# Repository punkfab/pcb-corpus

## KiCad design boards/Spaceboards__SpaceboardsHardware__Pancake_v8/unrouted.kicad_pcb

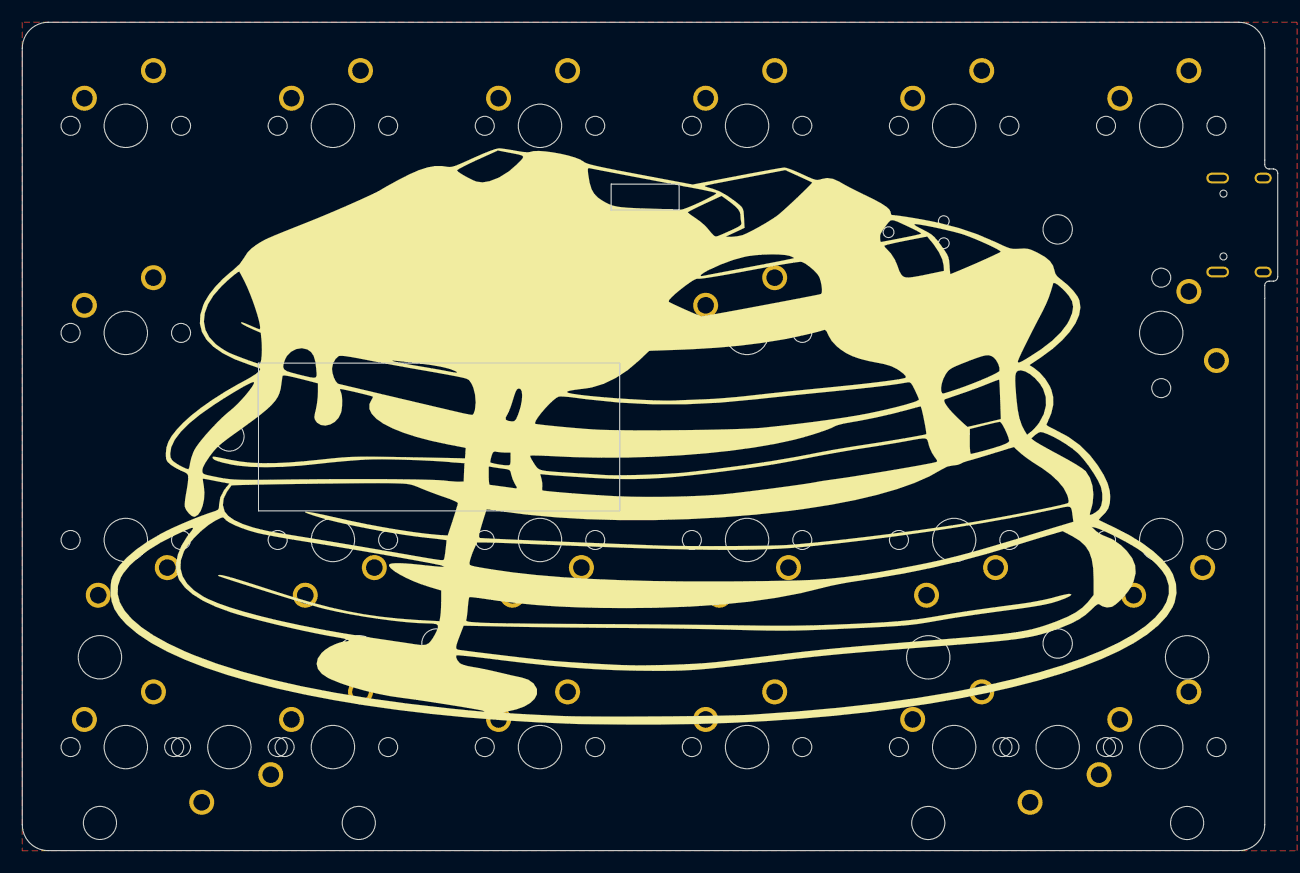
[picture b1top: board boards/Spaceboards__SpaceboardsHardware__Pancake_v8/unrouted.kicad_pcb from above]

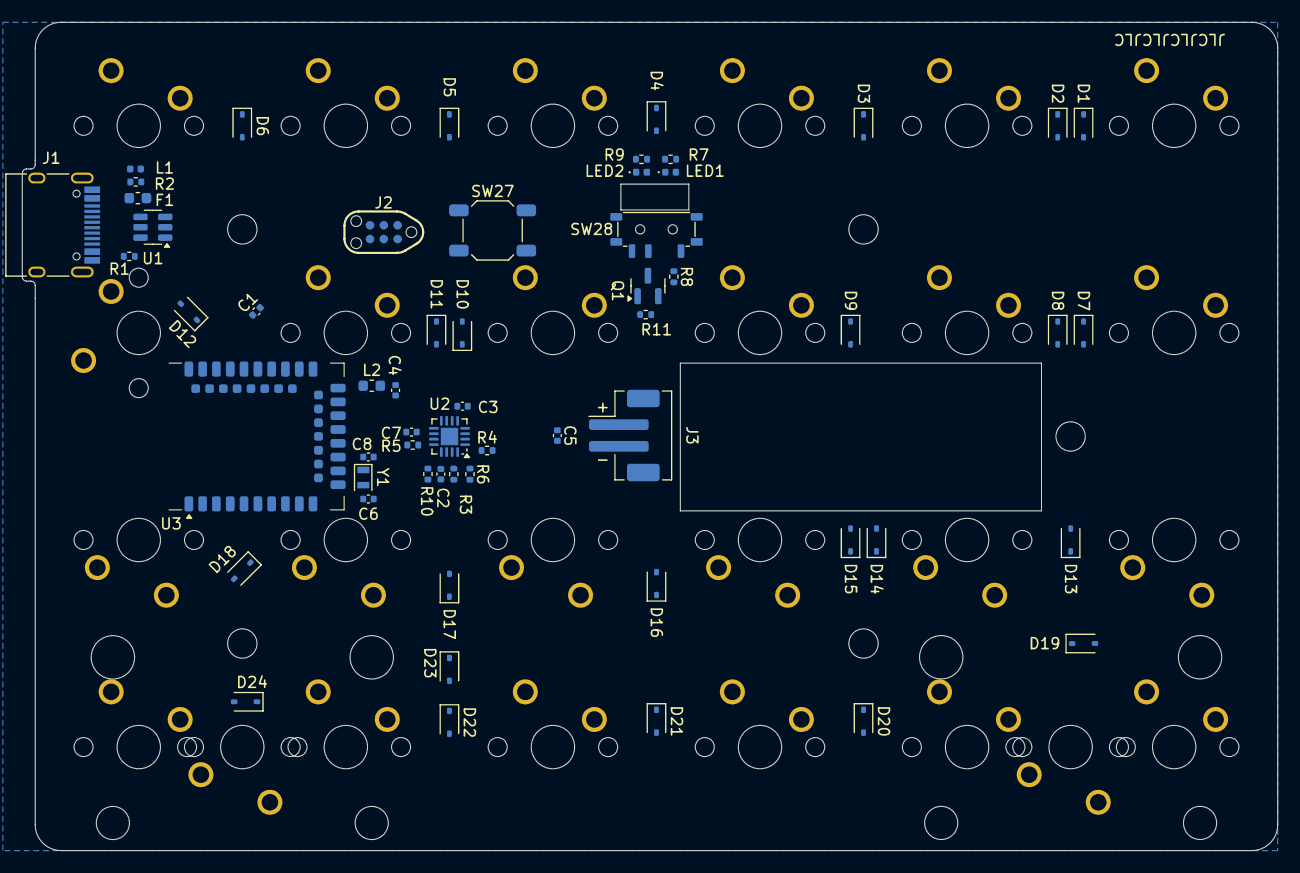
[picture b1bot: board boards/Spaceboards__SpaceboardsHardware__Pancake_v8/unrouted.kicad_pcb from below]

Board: 2 copper layers, 115.5 x 76.2 mm, 91 parts (58 on the bottom side), 62 nets, no tracks yet.

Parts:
C1, C2, C3, C5, C7: 4u7; C_0402_1005Metric
C4: 1u; C_0402_1005Metric
C6, C8: 12p; C_0402_1005Metric
D1, D2, D3, D4, D5, D6, D7, D8, D9, D10, D11, D12, D13, D14, D15, D16, D17, D18, D19, D20, D21, D22, D23, D24: D_Small; D_SOD-323
F1: 750 mA; Fuse_0603_1608Metric
H1, H2, H3, H4, H5: MountingHole; MountingHole_2.7mm_M2.5
J1: HRO_TYPE-C-31-M-14; USB_C_Receptacle_HRO_TYPE-C-31-M-12
J2: TC2030_SWD; CON_TC2030_outlined
J3: Battery; JST_PH_B2B-PH-SM4-TB_1x02-1MP_P2.00mm_Vertical
L1: BLM15PX121SN1D; L_0402_1005Metric
L2: 10 uH; L_0603_1608Metric
LED1: Orange; LED_0402_1005Metric
LED2: Blue; LED_0402_1005Metric
Q1: 2N7002; SOT-23
R1, R2: 5k1; R_0402_1005Metric
R3: 47k; R_0402_1005Metric
R4, R7, R9, R11: 10k; R_0402_1005Metric
R5: 1k5; R_0402_1005Metric
R6: 3k9; R_0402_1005Metric
R8: 100k; R_0402_1005Metric
R10: 100R; R_0402_1005Metric
S1, S2: MX_stab; STAB_MX_2u
SW1, SW2, SW3, SW4, SW5, SW6, SW7, SW8, SW9, SW10, SW11, SW12, SW13, SW14, SW15, SW16, SW17, SW18, SW19, SW20, SW21, SW22, SW23, SW24, SW25, SW26: SW_Push_45deg; SW_MX_1u
SW27: RST; SW_SPST_SKQG_WithStem
SW28: PWR; SW_MSK12C02-HB
U1: SRV05-4; SOT-23-6
U2: BQ24075; VQFN-16-1EP_3x3mm_P0.5mm_EP1.6x1.6mm
U3: nRF52840_E73-2G4M08S1C
Y1: 32.768 KHz; Crystal_SMD_2012-2Pin_2.0x1.2mm

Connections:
+5V: C1.1, C2.1, F1.1, R10.1, U1.5 (VP), U2.13 (IN), U3.27 (VBUS)
+BATT: C5.1, J3.1, R8.2, U2.2 (BAT), U2.3 (BAT)
+VSW: C3.1, C7.1, LED1.2 (A), U2.6 (EN1), U2.10 (OUT), U2.11 (OUT), U3.23 (VDDH)
/ILIM: R5.1, U2.12 (ILIM)
/TMR: R3.1, U2.14 (TMR)
BOOT: R9.1, U3.10 (P0.30/AIN6)
DCCH: L2.1, U3.25 (DCCH)
GND: C1.2, C2.2, C3.2, C4.2, C5.2, C6.2, C7.2, C8.2, J1.A1 (GND), J1.A12 (GND), J1.B1 (GND), J1.B12 (GND), J1.S1 (SHIELD), J2.5 (GND), J3.2, LED2.1 (K), Q1.2 (S), R1.1, R2.1, R3.2, R4.2, R5.2, R6.2, R11.2, SW27.2, SW28.3 (C), U1.2 (VN), U2.4 (~CE), U2.5 (EN2), U2.8 (VSS), U2.17 (VSS), U3.5 (GND), U3.21 (GND), U3.24 (GND)
unnamed: D1.2 (A), SW1.1
unnamed: D2.2 (A), SW2.1
unnamed: D3.2 (A), SW3.1
unnamed: D4.2 (A), SW4.1
unnamed: D5.2 (A), SW5.1
unnamed: D6.2 (A), SW6.1
unnamed: D7.2 (A), SW7.1
unnamed: D8.2 (A), SW8.1
unnamed: D9.2 (A), SW9.1
unnamed: D10.2 (A), SW10.1
unnamed: D11.2 (A), SW11.1
unnamed: D12.2 (A), SW12.1
unnamed: D13.2 (A), SW13.1
unnamed: D14.2 (A), SW14.1
unnamed: D15.2 (A), SW15.1
unnamed: D16.2 (A), SW16.1
unnamed: D17.2 (A), SW17.1
unnamed: D18.2 (A), SW18.1
unnamed: D19.2 (A), SW19.2, SW20.1
unnamed: D20.2 (A), SW21.1
unnamed: D21.2 (A), SW22.1
unnamed: D22.2 (A), SW23.1
unnamed: D23.2 (A), SW24.1
unnamed: D24.2 (A), SW25.2, SW26.1
unnamed: F1.2, L1.2
unnamed: J1.A5 (CC1), R2.2
unnamed: J1.B5 (CC2), R1.2
unnamed: LED1.1 (K), R7.2
unnamed: LED2.2 (A), R9.2
unnamed: Q1.1 (G), R10.2, R11.1
unnamed: R8.1, SW28.1 (A)
unnamed: R6.1, U2.16 (ISET)
unnamed: R4.1, U2.1 (TS)
unnamed: R7.1, U2.9 (~CHG)
unnamed: C6.1, U3.11 (P0.00/XL1), Y1.2
unnamed: C8.1, U3.13 (P0.01/XL2), Y1.1
RST: J2.3 (~RST), SW27.1, U3.26 (P0.18/~RESET)
SWDCLK: J2.4 (SWCLK), U3.39 (SWDCLK)
SWDIO: J2.2 (SWDIO), U3.37 (SWDIO)
SYSOFF: Q1.3 (D), SW28.2 (B), U2.15 (SYSOFF)
USB-D+: J1.A6 (D+), J1.B6 (D+), U1.6 (IO4), U3.31 (D+)
USB-D-: J1.A7 (D-), J1.B7 (D-), U1.1 (IO1), U3.29 (D-)
VBUS: J1.A4 (VBUS), J1.A9 (VBUS), J1.B4 (VBUS), J1.B9 (VBUS), L1.1
VDD: C4.1, J2.1 (VCC), L2.2, U3.19 (VDD)
c0: SW1.2, SW7.2, SW13.2, SW19.1, SW20.2, U3.8 (P0.29/AIN5)
c1: SW2.2, SW8.2, SW14.2, SW21.2, U3.9 (P0.31/AIN7)
c2: SW3.2, SW9.2, SW15.2, SW22.2, U3.7 (P0.02/AIN0)
c3: SW4.2, SW10.2, SW16.2, SW23.2, U3.6 (P1.13)
c4: SW5.2, SW11.2, SW17.2, SW24.2, U3.4 (P0.28/AIN4)
c5: SW6.2, SW12.2, SW18.2, SW25.1, SW26.2, U3.1 (P1.11)
r0: D1.1 (K), D2.1 (K), D3.1 (K), D4.1 (K), D5.1 (K), D6.1 (K), U3.41 (P0.09/NFC1)
r1: D7.1 (K), D8.1 (K), D9.1 (K), D10.1 (K), D11.1 (K), D12.1 (K), U3.43 (P0.10/NFC2)
r2: D13.1 (K), D14.1 (K), D15.1 (K), D16.1 (K), D17.1 (K), D18.1 (K), U3.3 (P0.03/AIN1)
r3: D19.1 (K), D20.1 (K), D21.1 (K), D22.1 (K), D23.1 (K), D24.1 (K), U3.2 (P1.10)

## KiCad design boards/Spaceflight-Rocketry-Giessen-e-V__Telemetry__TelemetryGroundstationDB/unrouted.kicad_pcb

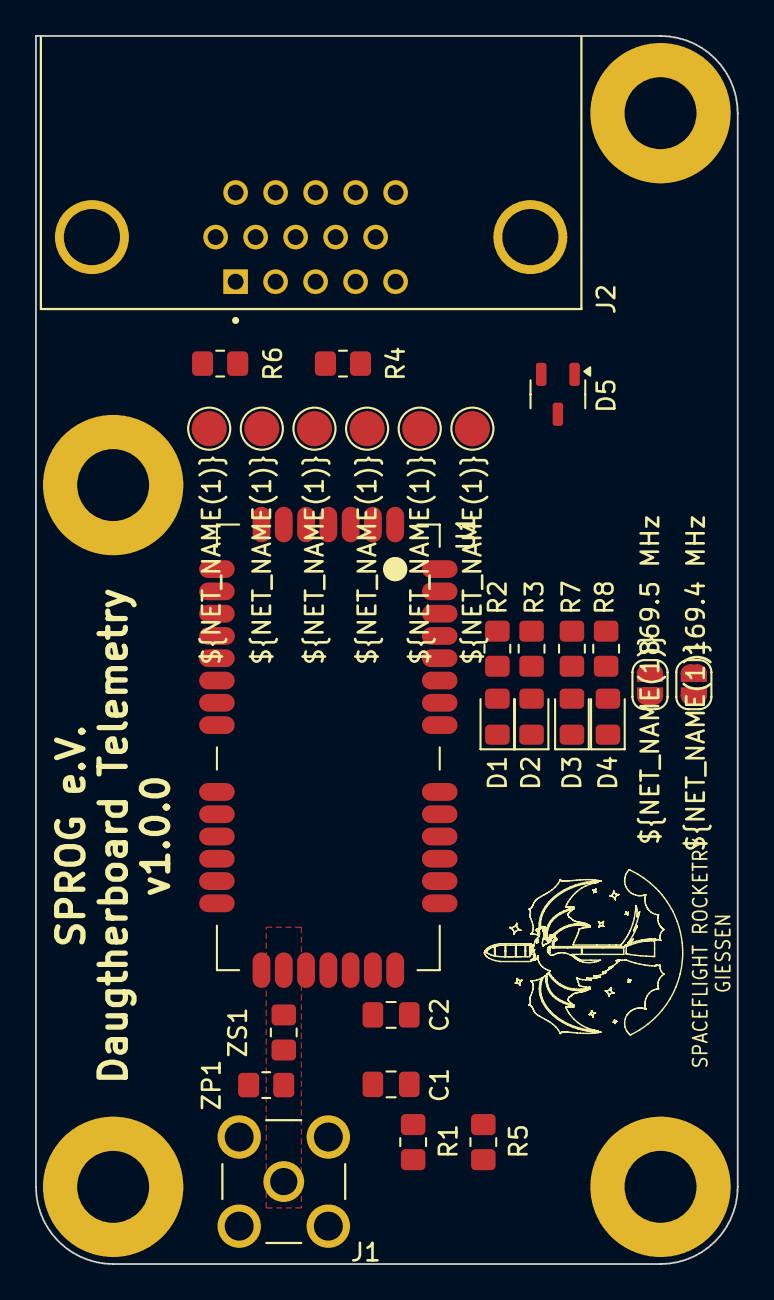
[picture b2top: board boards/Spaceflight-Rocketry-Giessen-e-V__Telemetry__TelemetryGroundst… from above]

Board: 2 copper layers, 40.0 x 70.0 mm, 32 parts (0 on the bottom side), 19 nets, no tracks yet.

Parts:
C1: 1 nF; C_0805_2012Metric_Pad1.18x1.45mm_HandSolder
C2: 1 uf; C_0805_2012Metric_Pad1.18x1.45mm_HandSolder
D1, D3, D4: green; LED_0805_2012Metric_Pad1.15x1.40mm_HandSolder
D2: yellow; LED_0805_2012Metric_Pad1.15x1.40mm_HandSolder
D5: WE-TVS_SOT23-3L_824021; SOT-23-3
J1: RFPC-SMA27-F; GRADCONN_RFPC-SMA27-F
J2: ICD15S13E4GV00LF; AMPHENOL_ICD15S13E4GV00LF[1]
JP1, JP2: SolderJumper_2_Open; Solder Jumper
M1, M2, M3, M4: M4 Mounting Hole
R1: 2k7; R_0805_2012Metric_Pad1.20x1.40mm_HandSolder
R2, R3: 560R; R_0805_2012Metric_Pad1.20x1.40mm_HandSolder
R4, R5, R6: 5k6; R_0805_2012Metric_Pad1.20x1.40mm_HandSolder
R7, R8: 560 Ohm; R_0805_2012Metric_Pad1.20x1.40mm_HandSolder
TP1, TP2, TP3, TP4, TP5, TP6: TestPoint; Test Point
U1: RC1780HP-RC232; Radiocrafts RC1780HP-RC232
ZP1: R_0805_2012Metric_Pad1.20x1.40mm_HandSolder
ZS1: R_0805_2012Metric_Pad1.20x1.40mm_HandSolder

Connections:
+3V3: C2.1, D5.2, J2.9, J2.10, JP2.1 (A), R4.2, R5.2, R6.2, R7.1, U1.13 (VCC)
+5V: D5.1, J2.14, J2.15, JP1.1 (A), R8.1
CFG: J2.3, R4.1, TP5.1, U1.4 (CONFIG)
CTS: J2.5, TP4.1, U1.2 (CTS/RXTX)
GND: C1.2, C2.2, D1.1 (K), D2.1 (K), D3.1 (K), D4.1 (K), D5.3, J1.G1, J1.G2, J1.G3, J1.G4, J2.7, J2.8, J2.11, J2.12, J2.13, J2.SH1 (SHIELD), J2.SH2 (SHIELD__1), M1.1, M2.1, M3.1, M4.1, U1.1 (GND), U1.7 (GND), U1.8 (GND), U1.10 (GND), U1.14 (GND), ZP1.2
unnamed: D1.2 (A), R2.1
unnamed: D2.2 (A), R3.1
unnamed: D3.2 (A), R7.2
unnamed: D4.2 (A), R8.2
unnamed: J1.1, ZP1.1, ZS1.2
unnamed: JP1.2 (B), JP2.2 (B), U1.41 (VCC_PA)
unnamed: R2.2, U1.29 (D1)
unnamed: R3.2, U1.30 (D2)
unnamed: C1.1, R1.1, U1.12 (RESET)
unnamed: U1.9 (RF), ZS1.1
RST: J2.6, R1.2, R5.1, TP3.1
RTS: J2.4, TP6.1, U1.3 (RTS/SLEEP)
RX: J2.2, TP2.1, U1.5 (TXD)
TX: J2.1, R6.1, TP1.1, U1.6 (RXD)

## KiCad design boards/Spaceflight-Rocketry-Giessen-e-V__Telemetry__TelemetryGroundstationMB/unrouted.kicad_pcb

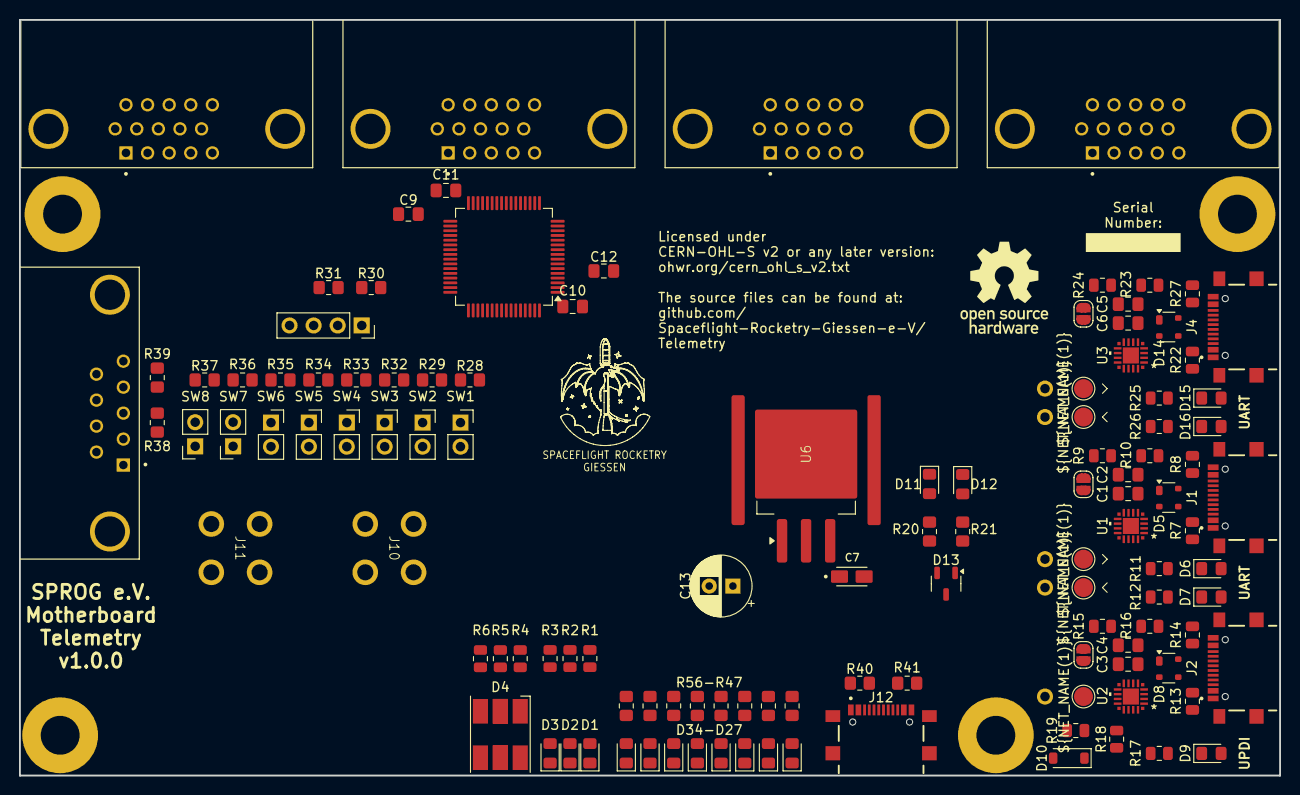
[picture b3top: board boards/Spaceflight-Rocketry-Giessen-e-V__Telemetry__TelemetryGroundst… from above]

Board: 2 copper layers, 133.0 x 79.8 mm, 122 parts (0 on the bottom side), 111 nets, no tracks yet.

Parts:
C1, C3, C6: 4.7u; C_0805_2012Metric_Pad1.18x1.45mm_HandSolder
C2, C4, C5: 0.1u; C_0805_2012Metric_Pad1.18x1.45mm_HandSolder
C7: 10u Tantal; CAPMP3216X180N
C9, C10, C11, C12: 1u; C_0805_2012Metric_Pad1.18x1.45mm_HandSolder
C13: 100u Elko; CP_Radial_D6.3mm_P2.50mm
D1, D2, D3, D7, D16, D27, D28, D29, D30, D31, D32, D33, D34: orange; LED_0805_2012Metric_Pad1.15x1.40mm_HandSolder
D4: Cree RGB LED
D5, D8, D14: SP0503BAHT; SOT-143
D6, D11, D12, D15: green; LED_0805_2012Metric_Pad1.15x1.40mm_HandSolder
D9: red; LED_0805_2012Metric_Pad1.15x1.40mm_HandSolder
D10: BAT43; D_SOD-123
D13: WE-TVS_SOT23-3L_824021; SOT-23-3
J1, J2, J4, J12: USB-C; GCT_USB4216-03-A_REVA
J3, J5, J6, J7: ICD15S13E4GV00LF; AMPHENOL_ICD15S13E4GV00LF[1]
J8: LD09S33E4GV00LF; AMPHENOL_LD09S33E4GV00LF
J9: Conn_01x04_Socket; PinSocket_1x04_P2.54mm_Vertical
J10: Conn_01x01; Banana_CT3151-0
J11: Conn_01x01; Banana_CT3151-2
JP1, JP2, JP3: SolderJumper_2_Open; Solder Jumper
M1, M2, M3, M4: M4 Mounting Hole
R1, R2, R3, R4, R5, R6, R11, R12, R17, R25, R26: 560R; R_0805_2012Metric
R7, R8, R13, R14, R22, R27: 5k1; R_0805_2012Metric
R9, R15, R24: 47k; R_0805_2012Metric
R10, R16, R23: 22k; R_0805_2012Metric
R18, R19: 470R; R_0805_2012Metric
R20, R21, R37, R47, R48, R51, R52, R53, R54, R55, R56: 560R; R_0805_2012Metric_Pad1.20x1.40mm_HandSolder
R28, R29, R30, R31, R32, R33, R34, R35, R36, R38, R39: 5k6; R_0805_2012Metric_Pad1.20x1.40mm_HandSolder
R40, R41: 5k1; R_0805_2012Metric_Pad1.20x1.40mm_HandSolder
SW1, SW2, SW3, SW4, SW5, SW6, SW7: SW_Push; PinSocket_1x02_P2.54mm_Vertical
SW8: SW_DIP_x01; PinSocket_1x02_P2.54mm_Vertical
TP1, TP2, TP3, TP6, TP7: TestPoint; Test Point
U1, U2, U3: CP2102N; QFN20_CP2102N_SIL
U5: AVR128DB64x-xPT; TQFP-64_10x10mm_P0.5mm
U6: MIC29300-3.3WU-TR; MIC29300

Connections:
+3V3: C1.1, C2.1, C3.1, C4.1, C5.1, C6.1, C7.1, C9.1, C10.1, C11.2, C12.2, D6.2 (A), D7.2 (A), D9.2 (A), D13.2, D15.2 (A), D16.2 (A), J3.9, J3.10, J5.9, J5.10, J6.9, J6.10, J7.9, J7.10, R20.1, R30.2, R31.2, R37.1, U1.6 (VDD), U1.7 (VREGIN), U2.6 (VDD), U2.7 (VREGIN), U3.6 (VDD), U3.7 (VREGIN), U5.6 (VDD), U5.20 (VDDIO2), U5.34 (AVDD), U5.56 (VDD), U6.3 (OUT)
+5V: C13.1, D13.1, J3.14, J3.15, J5.14, J5.15, J6.14, J6.15, J7.14, J7.15, J9.3, J11.1, J12.A4_B9 (VBUS_A), J12.B4_A9 (VBUS_B), R21.1, U6.1 (IN)
Button1: R28.1, SW1.1, U5.54 (PG2)
Button2: R29.1, SW2.1, U5.50 (~RESET/PF6)
Button3: R32.1, SW3.1, U5.49 (PF5)
Button4: R33.1, SW4.1, U5.48 (PF4)
Button5: R34.1, SW5.1, U5.47 (PF3)
Button6: R35.1, SW6.1, U5.46 (PF2)
D01: J3.3, U5.1 (PA3)
D02: J3.4, U5.64 (PA2)
D03: J3.5, U5.63 (XTALHF2/PA1)
D04: J3.6, U5.4 (PA6)
D11: J5.3, U5.22 (PC4)
D12: J5.4, U5.19 (PC3)
D13: J5.5, U5.18 (PC2)
D14: J5.6, U5.23 (PC5)
D21: J6.3, U5.40 (PE4)
D22: J6.4, U5.39 (PE3)
D23: J6.5, U5.38 (PE2)
D24: J6.6, U5.41 (PE5)
D31: J7.3, U5.12 (PB4)
D32: J7.4, U5.11 (PB3)
D33: J7.5, U5.10 (PB2)
D34: J7.6, U5.13 (PB5)
D+1: D5.4 (K), J1.A6 (DP1), J1.B6 (DP2), U1.4 (D+)
D+2: D8.4 (K), J2.A6 (DP1), J2.B6 (DP2), U2.4 (D+)
D+3: D14.4 (K), J4.A6 (DP1), J4.B6 (DP2), U3.4 (D+)
D-1: D5.3 (K), J1.A7 (DN1), J1.B7 (DN2), U1.5 (D-)
D-2: D8.3 (K), J2.A7 (DN1), J2.B7 (DN2), U2.5 (D-)
D-3: D14.3 (K), J4.A7 (DN1), J4.B7 (DN2), U3.5 (D-)
GND: C1.2, C2.2, C3.2, C4.2, C5.2, C6.2, C7.2, C9.2, C10.2, C11.1, C12.1, C13.2, D1.1 (K), D2.1 (K), D3.1 (K), D4.4 (KB), D4.5 (KR), D4.6 (KR), D5.1 (A), D8.1 (A), D11.1 (K), D12.1 (K), D13.3, D14.1 (A), D27.1 (K), D28.1 (K), D29.1 (K), D30.1 (K), D31.1 (K), D32.1 (K), D33.1 (K), D34.1 (K), J1.A1_B12 (GND_A), J1.B1_A12 (GND_B), J1.SH1 (SHIELD), J1.SH2 (SHIELD), J1.SH3 (SHIELD), J1.SH4 (SHIELD), J2.A1_B12 (GND_A), J2.B1_A12 (GND_B), J2.SH1 (SHIELD), J2.SH2 (SHIELD), J2.SH3 (SHIELD), J2.SH4 (SHIELD), J3.7, J3.8, J3.11, J3.12, J3.13, J3.SH1 (SHIELD), J3.SH2 (SHIELD__1), J4.A1_B12 (GND_A), J4.B1_A12 (GND_B), J4.SH1 (SHIELD), J4.SH2 (SHIELD), J4.SH3 (SHIELD), J4.SH4 (SHIELD), J5.7, J5.8, J5.11, J5.12, J5.13, J5.SH1 (SHIELD), J5.SH2 (SHIELD__1), J6.7, J6.8, J6.11, J6.12, J6.13, J6.SH1 (SHIELD), J6.SH2 (SHIELD__1), J7.7, J7.8, J7.11, J7.12, J7.13, J7.SH1 (SHIELD), J7.SH2 (SHIELD__1), J8.5, J8.SH1 (SHIELD), J8.SH2 (SHIELD__1), J9.4, J10.1, J12.A1_B12 (GND_A), J12.B1_A12 (GND_B), J12.SH1 (SHIELD), J12.SH2 (SHIELD), J12.SH3 (SHIELD), J12.SH4 (SHIELD), JP1.2 (B), JP2.2 (B), JP3.2 (B), M1.1, M2.1, M3.1, M4.1, R7.2, R8.2, R9.2, R13.2, R14.2, R15.2, R22.2, R24.2, R27.2, R28.2, R29.2, R32.2, R33.2, R34.2, R35.2, R36.2, R38.2, R39.2, R40.2, R41.2, U1.3 (GND), U1.12 (GND), U1.21 (GND), U2.3 (GND), U2.12 (GND), U2.21 (GND), U3.3 (GND), U3.12 (GND), U3.21 (GND), U5.7 (GND), U5.21 (GND), U5.35 (AGND), U5.57 (GND), U6.2 (GND), U6.4
Input1: J8.3, R38.1, U5.43 (PE7)
Input2: J8.4, R39.1, U5.42 (PE6)
LED 1: R1.1, U5.62 (XTALHF1/PA0)
LED 2: R2.1, U5.61 (PG7)
LED 3: R3.1, U5.60 (PG6)
LED B: R6.1, U5.55 (PG3)
LED G: R5.1, U5.58 (PG4)
LED R: R4.1, U5.59 (PG5)
MasterButton: R36.1, SW1.2, SW2.2, SW3.2, SW4.2, SW5.2, SW6.2, SW7.1
unnamed: D1.2 (A), R1.2
unnamed: D2.2 (A), R2.2
unnamed: D3.2 (A), R3.2
unnamed: D4.3 (AB), R6.2
unnamed: D4.2 (AG), R5.2
unnamed: D4.1 (AR), R4.2
unnamed: D6.1 (K), R11.1
unnamed: D7.1 (K), R12.1
unnamed: D9.1 (K), R17.1
unnamed: D10.2 (A), R19.2, U2.17 (RXD)
unnamed: D10.1 (K), R18.1
unnamed: D11.2 (A), R20.2
unnamed: D12.2 (A), R21.2
unnamed: D15.1 (K), R25.1
unnamed: D16.1 (K), R26.1
unnamed: D27.2 (A), R47.1
unnamed: D28.2 (A), R48.1
unnamed: D29.2 (A), R51.1
unnamed: D30.2 (A), R52.1
unnamed: D31.2 (A), R53.1
unnamed: D32.2 (A), R54.1
unnamed: D33.2 (A), R55.1
unnamed: D34.2 (A), R56.1
unnamed: J1.A5 (CC1), R7.1
unnamed: J1.B5 (CC2), R8.1
unnamed: J2.A5 (CC1), R13.1
unnamed: J2.B5 (CC2), R14.1
unnamed: J4.A5 (CC1), R22.1
unnamed: J4.B5 (CC2), R27.1
unnamed: J12.A5 (CC1), R40.1
unnamed: J12.B5 (CC2), R41.1
unnamed: JP1.1 (A), U1.15 (~CTS)
unnamed: JP2.1 (A), U2.15 (~CTS)
unnamed: JP3.1 (A), U3.15 (~CTS)
unnamed: R37.2, SW8.2
unnamed: SW7.2, SW8.1
unnamed: R9.1, R10.2, U1.8 (VBUS)
unnamed: R12.2, U1.19 (~RXT/GPIO.3)
unnamed: R11.2, U1.20 (~TXT/GPIO.2)
unnamed: R18.2, U2.18 (TXD)
unnamed: R15.1, R16.2, U2.8 (VBUS)
unnamed: R17.2, U2.20 (~TXT/GPIO.2)
unnamed: R23.2, R24.1, U3.8 (VBUS)
unnamed: R26.2, U3.19 (~RXT/GPIO.3)
unnamed: R25.2, U3.20 (~TXT/GPIO.2)
unnamed: R47.2, U5.26 (PD0)
unnamed: R48.2, U5.27 (PD1)
unnamed: R51.2, U5.28 (PD2)
unnamed: R52.2, U5.29 (PD3)
unnamed: R53.2, U5.30 (PD4)
unnamed: R54.2, U5.31 (PD5)
unnamed: R55.2, U5.32 (PD6)
unnamed: R56.2, U5.33 (VREFA/PD7)
RX0: J3.2, U5.3 (PA5)
RX1: J5.2, U5.17 (PC1)
RX2: TP7.1, U3.18 (TXD), U5.45 (XTAL32K2/PF1)
RX3: J7.2, U5.9 (PB1)
RX4: J6.2, U5.37 (PE1)
RX5: TP1.1, U1.18 (TXD), U5.53 (PG1)
SCL0: J9.1, R30.1, U5.25 (PC7)
SDA0: J9.2, R31.1, U5.24 (PC6)
TX0: J3.1, U5.2 (PA4)
TX1: J5.1, U5.16 (PC0)
TX2: TP6.1, U3.17 (RXD), U5.44 (XTAL32K1/PF0)
TX3: J7.1, U5.8 (PB0)
TX4: J6.1, U5.36 (PE0)
TX5: TP2.1, U1.17 (RXD), U5.52 (PG0)
UPDI: R19.1, TP3.1, U5.51 (UPDI)
VBUS1: D5.2 (K), J1.A4_B9 (VBUS_A), J1.B4_A9 (VBUS_B), R10.1
VBUS2: D8.2 (K), J2.A4_B9 (VBUS_A), J2.B4_A9 (VBUS_B), R16.1
VBUS3: D14.2 (K), J4.A4_B9 (VBUS_A), J4.B4_A9 (VBUS_B), R23.1

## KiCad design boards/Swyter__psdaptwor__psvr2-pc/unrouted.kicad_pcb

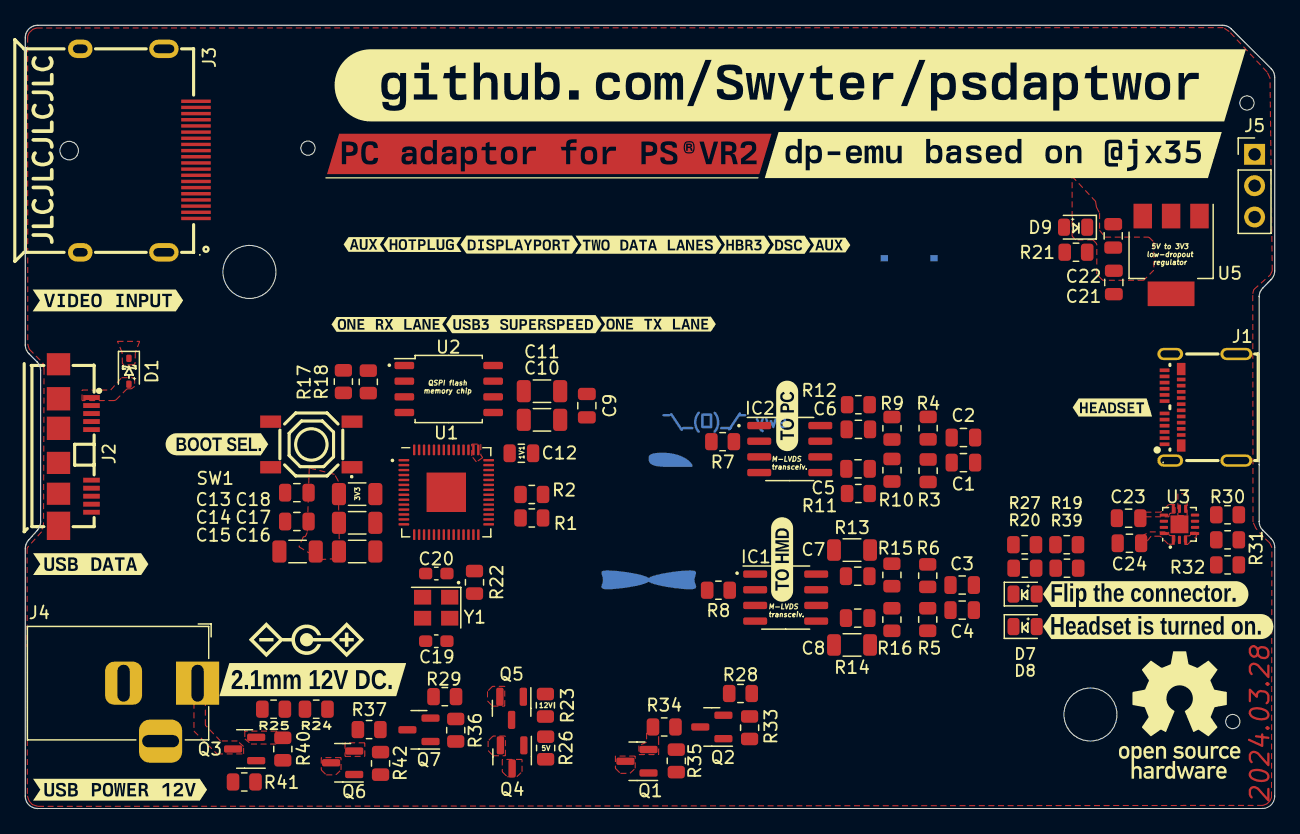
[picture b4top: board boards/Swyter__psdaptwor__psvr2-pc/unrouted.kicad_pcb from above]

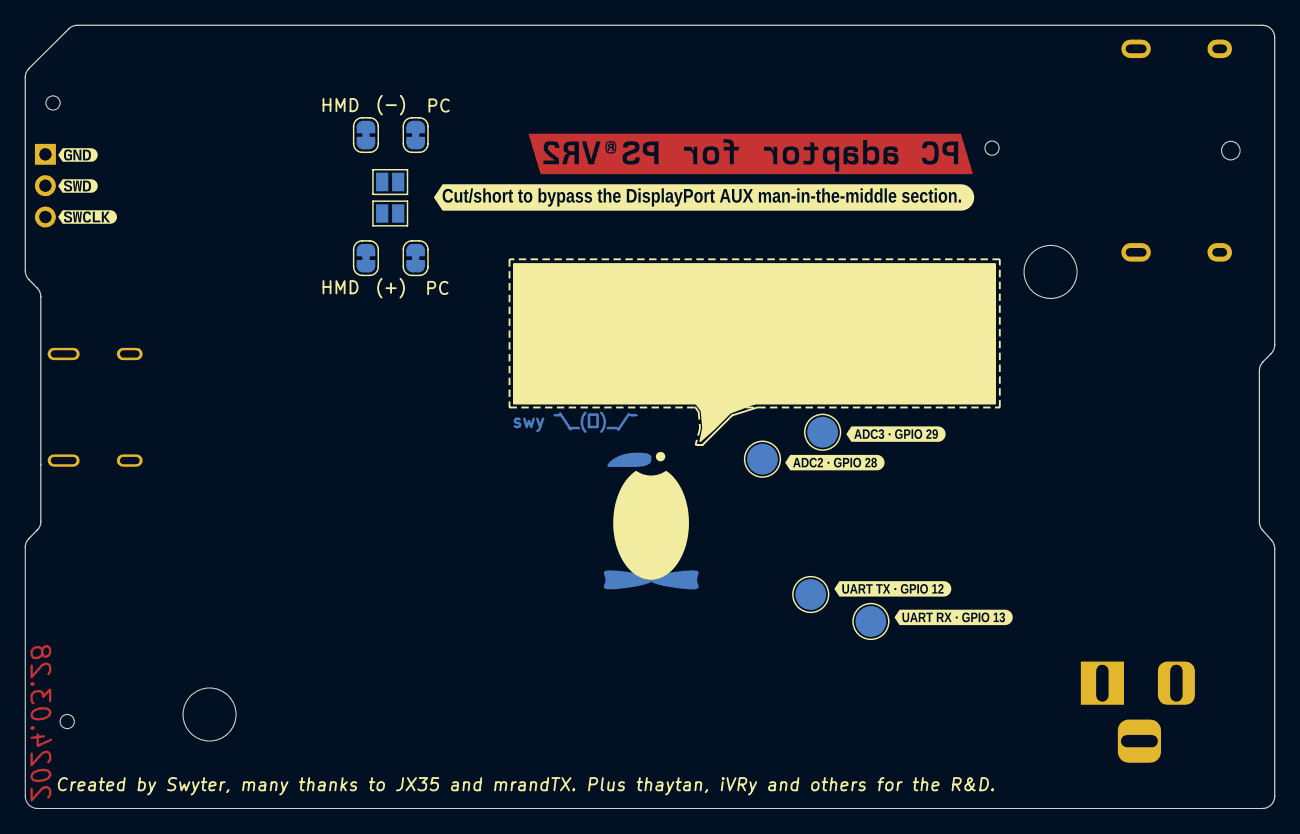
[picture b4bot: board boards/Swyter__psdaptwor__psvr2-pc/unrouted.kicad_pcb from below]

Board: 4 copper layers, 101.3 x 63.5 mm, 135 parts (18 on the bottom side), 89 nets, no tracks yet.

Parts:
C1, C3, C5, C6, C7, C8: 100n; C_0805_2012Metric
C2, C4: 1n; C_0805_2012Metric
C9, C12, C13, C14, C22: 1uF; C_0805_2012Metric
C10, C11, C15, C16, C17, C18: 100uF; C_1206_3216Metric
C19, C20: 33pF; C_0603_1608Metric_Pad1.08x0.95mm_HandSolder
C21: 22uF; C_0805_2012Metric
C23, C24: 470pF; C_0805_2012Metric
D1: 1N5819WS; D_SOD-323
D7, D8, D9: LED; LED_0805_2012Metric
IC1, IC2: SN65MLVD200ADR; SOIC-8_3.9x4.9mm_P1.27mm
J1: USB_C_Receptacle; USB-C-SMD_TYPE-C-USB-18
J2: USB3_B_Micro; USB-SMD_692622030100
J3: DP_47272; CONN-SMD_472720001
J4: Barrel_Jack_Switch; BarrelJack_Horizontal
J5: Conn_01x02_Pin; PinHeader_1x03_P2.54mm_Vertical
JP1, JP2: SolderJumper_2_Open; SolderJumper-2_P1.3mm_Open_Pad1.0x1.5mm
JP3, JP5, JP6: SolderJumper_2_CLOSED; SolderJumper-2_P1.3mm_Bridged_RoundedPad1.0x1.5mm
JP4: SolderJumper_2_Open; SolderJumper-2_P1.3mm_Bridged_RoundedPad1.0x1.5mm
M4_MOUNT_HOLE_DOWN, M4_MOUNT_HOLE_UP: MountingHole_4.3mm_M4
Q1, Q3, Q4, Q5, Q6: AO3401A; SOT-23
Q2, Q7: MMBT2222A; SOT-23
R1, R2: 33R; R_0805_2012Metric
R3, R5: 3K3; R_0805_2012Metric
R4, R6: 1K5; R_0805_2012Metric
R7, R8, R18, R28, R29, R34, R37, R41: 10K; R_0805_2012Metric
R9, R10, R15, R16, R19: 51; R_0805_2012Metric
R11, R12: 1M; R_0805_2012Metric
R13, R14: 100K; R_1206_3216Metric
R17, R33, R36: 1K; R_0805_2012Metric
R20, R21, R27: 120; R_0805_2012Metric
R22: 100; R_0805_2012Metric
R23, R26: 100K; R_0805_2012Metric
R24: 51K; R_0805_2012Metric
R25: 8K2; R_0805_2012Metric
R30, R31, R32: 4K7; R_0805_2012Metric
R35, R40, R42: 6K8; R_0805_2012Metric
R39: 33; R_0805_2012Metric
SMT_BOTTOM_RIGHT: MountingHole_2.1mm
SMT_TOP_LEFT: MountingHole_2.1mm
SMT_TOP_RIGHT: MountingHole_2.1mm
SW1: SW_Push; SW-SMD_4P-L5.1-W5.1-P3.70-LS6.5-TL-2
TP1, TP2, TP3, TP4: TestPoint_Small; TestPoint_Pad_D2.5mm
U1: RP2040 microcontroller; QFN-56-1EP_7x7mm_P0.4mm_EP3.2x3.2mm
U2: W25Q128JVS; SOIC-8_5.23x5.23mm_P1.27mm
U3: FUSB302B01MPX; WQFN-14-1EP_2.5x2.5mm_P0.5mm_EP1.45x1.45mm
U5: AMS1117-3.3; SOT-223-3_TabPin2
Y1: 12MHz 20pF (X322512MSB4SI for JLC); Crystal_SMD_3225-4Pin_3.2x2.5mm
kibuzzard-65C6E5E2: G***; kibuzzard-65C6E5E2
kibuzzard-65C6E540: G***; kibuzzard-65C6E540
kibuzzard-65C0700D: G***; kibuzzard-65C0700D
kibuzzard-65C07004: G***; kibuzzard-65C07004
kibuzzard-65C07017: G***; kibuzzard-65C07017
kibuzzard-65E1F822: G***; kibuzzard-65E1F822
kibuzzard-65E1F853: G***; kibuzzard-65E1F853
kibuzzard-65E1FEE7: G***; kibuzzard-65E1FEE7
kibuzzard-65E1FEEE: G***; kibuzzard-65E1FEEE
kibuzzard-65E1FFC8: G***; kibuzzard-65E1FFC8
kibuzzard-65E7A09E: G***; kibuzzard-65E7A09E
kibuzzard-65E7A091: G***; kibuzzard-65E7A091
kibuzzard-65E7B531: G***; kibuzzard-65E7B531
kibuzzard-65E009D7: G***; kibuzzard-65E009D7
kibuzzard-65E024DE: G***; kibuzzard-65E024DE
kibuzzard-65E0054E: G***; kibuzzard-65E0054E
kibuzzard-65E91FE7: G***; kibuzzard-65E91FE7
kibuzzard-65E539B1: G***; kibuzzard-65E539B1
kibuzzard-65E00649: G***; kibuzzard-65E00649
kibuzzard-65E00656: G***; kibuzzard-65E00656
kibuzzard-65E00723: G***; kibuzzard-65E00723
kibuzzard-65E00862: G***; kibuzzard-65E00862
kibuzzard-65E00873: G***; kibuzzard-65E00873
kibuzzard-65E00902: G***; kibuzzard-65E00902
kibuzzard-65E00968: G***; kibuzzard-65E00968
kibuzzard-65E01491: G***; kibuzzard-65E01491
kibuzzard-65E20367: G***; kibuzzard-65E20367
kibuzzard-65EB850B: G***; kibuzzard-65EB850B
kibuzzard-65EB8511: G***; kibuzzard-65EB8511
kibuzzard-65F67D58: G***; kibuzzard-65F67D58
kibuzzard-65F683C1: G***; kibuzzard-65F683C1

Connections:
+1V1: C9.1, C10.1, C11.1, U1.23 (DVDD), U1.45 (VREG_VOUT), U1.50 (DVDD)
+3.3V: C12.1, C13.2, C14.2, C15.2, C16.2, C17.2, C18.2, C21.1, IC1.8 (VCC), IC2.8 (VCC), R3.1, R5.1, R18.2, R21.2, R30.2, R31.2, R32.2, U1.1 (IOVDD), U1.10 (IOVDD), U1.22 (IOVDD), U1.33 (IOVDD), U1.42 (IOVDD), U1.43 (ADC_AVDD), U1.44 (VREG_IN), U1.48 (USB_VDD), U1.49 (IOVDD), U2.8 (VCC), U3.3 (VDD), U3.4 (VDD), U3.12 (VCONN), U3.13 (VCONN), U5.2 (VO)
/ADC_OPT_A: TP3.1, U1.40 (GPIO28_ADC2)
/ADC_OPT_B: TP4.1, U1.41 (GPIO29_ADC3)
/CC1: C23.1, J1.A5 (CC1), U3.10 (CC1), U3.11 (CC1)
/CC2: C24.1, J1.B5 (CC2), U3.1 (CC2), U3.14 (CC2)
/DC_JACK_12V: Q3.2 (S), Q6.2 (S), R24.2, R37.2, R40.2
/DC_JACK_VOLT_SENSE: R24.1, R25.2, U1.38 (GPIO26_ADC0)
/HMD_AUX_N: J1.B8 (SBU2), JP2.1 (A), JP4.1 (A)
/HMD_AUX_P: J1.A8 (SBU1), JP1.1 (A), JP3.1 (A)
/HMD_AUX_TERMINATION_N: R14.2, U1.34 (GPIO22)
/HMD_AUX_TERMINATION_P: R13.1, U1.35 (GPIO23)
/HMD_ENABLE_VBUS: R28.2, R33.2, U1.28 (GPIO17)
/HMD_ENABLE_VBUS_12V: R29.2, R36.2, U1.27 (GPIO16)
/HMD_INNER_AUX_N: C8.2, JP4.2 (B), R14.1
/HMD_INNER_AUX_P: C7.2, JP3.2 (B), R13.2
/HMD_LVDS_D: IC1.4 (D), U1.13 (GPIO10)
/HMD_LVDS_DE: IC1.3 (DE), U1.12 (GPIO9)
/HMD_LVDS_R: IC1.1 (R), U1.9 (GPIO7)
/HMD_LVDS_~RE: IC1.2 (~RE), R8.1, U1.11 (GPIO8)
/HMD_TYC_INT: R32.1, U1.4 (GPIO2), U3.5 (INT_N)
/HMD_TYC_SCL: R31.1, U1.3 (GPIO1), U3.6 (SCL)
/HMD_TYC_SDA: R30.1, U1.2 (GPIO0), U3.7 (SDA)
/HMD_USB2_N: J1.A7 (D-), J1.B7 (D-), U1.30 (GPIO19)
/HMD_USB2_P: J1.A6 (D+), J1.B6 (D+), U1.29 (GPIO18)
/HMD_VBUS: J1.A4 (VBUS), J1.A9 (VBUS), J1.B4 (VBUS), J1.B9 (VBUS), Q1.3 (D), U3.2 (VBUS)
/LED_CONN_WRONG_ORIENT: R27.2, U1.17 (GPIO14)
/LED_HMD_IS_READY: R20.2, U1.18 (GPIO15)
/ML0_N: J1.A10 (RX2-), J3.10 (D0_N)
/ML0_P: J1.A11 (RX2+), J3.12 (D0_P)
/ML1_N: J1.B3 (TX2-), J3.7 (D1_N)
/ML1_P: J1.B2 (TX2+), J3.9 (D1_P)
/PC_AUX_N: J3.17 (AUX_N), JP2.2 (B), JP6.2 (B)
/PC_AUX_P: J3.15 (AUX_P), JP1.2 (B), JP5.2 (B)
/PC_AUX_TERMINATION_N: R11.2, U1.36 (GPIO24)
/PC_AUX_TERMINATION_P: R12.1, U1.37 (GPIO25)
/PC_HPD: J3.18 (HPD), U1.14 (GPIO11)
/PC_INNER_AUX_N: C5.2, JP6.1 (A), R11.1
/PC_INNER_AUX_P: C6.2, JP5.1 (A), R12.2
/PC_LVDS_D: IC2.4 (D), U1.8 (GPIO6)
/PC_LVDS_DR: IC2.3 (DE), U1.7 (GPIO5)
/PC_LVDS_R: IC2.1 (R), U1.5 (GPIO3)
/PC_LVDS_~RE: IC2.2 (~RE), R7.1, U1.6 (GPIO4)
/PC_USB2_INNER_N: R2.2, U1.46 (USB_DM)
/PC_USB2_INNER_P: R1.2, U1.47 (USB_DP)
/PC_USB2_N: J2.2 (D-), R2.1
/PC_USB2_P: J2.3 (D+), R1.1
/PC_VBUS_5V: C22.1, D1.1 (K), Q4.1 (G), Q5.3 (D), R26.2, U5.3 (VI)
/SSRX_N: J1.B10 (RX1-), J2.6 (SSTX-)
/SSRX_P: J1.B11 (RX1+), J2.7 (SSTX+)
/SSTX_N: J1.A3 (TX1-), J2.9 (SSRX-)
/SSTX_P: J1.A2 (TX1+), J2.10 (SSRX+)
/SWCLK: J5.3, U1.24 (SWCLK)
/SWD: J5.2, U1.25 (SWD)
/UART_RX: TP2.1, U1.16 (GPIO13)
/UART_TX: TP1.1, U1.15 (GPIO12)
/VBUS_12V: Q4.3 (D), Q5.1 (G), Q6.3 (D), R23.2
/V_BIAS_HMD: C3.1, C4.1, R5.2, R6.1, R15.2, R16.1
/V_BIAS_PC: C1.1, C2.1, R3.2, R4.1, R9.2, R10.1
GND: C1.2, C2.2, C3.2, C4.2, C9.2, C10.2, C11.2, C12.2, C13.1, C14.1, C15.1, C16.1, C17.1, C18.1, C19.2, C20.2, C21.2, C22.2, C23.2, C24.2, D7.1 (K), D8.1 (K), D9.1 (K), IC1.5 (GND), IC2.5 (GND), J1.0, J1.A1 (GND), J1.A12 (GND), J1.B1 (GND), J1.B12 (GND), J2.5 (GND), J2.8 (DRAIN), J2.11 (SHIELD), J3.2 (GND), J3.5 (GND), J3.8 (GND), J3.11 (GND), J3.16 (GND), J3.21, J3.22, J3.23, J3.24, J4.2, J4.3, J5.1, Q2.2 (E), Q7.2 (E), R4.2, R6.2, R7.2, R8.2, R23.1, R25.1, R26.1, R28.1, R29.1, R41.2, SW1.1, SW1.2, U1.19 (TESTEN), U1.57 (GND), U2.4 (GND), U3.8 (GND), U3.9 (GND), U3.15 (GND), U5.1 (GND), Y1.2, Y1.4
unnamed: C20.1, R22.1, Y1.1
unnamed: D1.2 (A), J2.1 (VBUS)
unnamed: D7.2 (A), R19.1
unnamed: D8.2 (A), R39.1
unnamed: D9.2 (A), R21.1
unnamed: C8.1, IC1.6 (A), R16.2
unnamed: C7.1, IC1.7 (B), R15.1
unnamed: C5.1, IC2.6 (A), R10.2
unnamed: C6.1, IC2.7 (B), R9.1
unnamed: Q1.1 (G), R34.1, R35.2
unnamed: Q1.2 (S), Q4.2 (S), Q5.2 (S), R34.2
unnamed: Q2.1 (B), R33.1
unnamed: Q2.3 (C), R35.1
unnamed: J4.1, Q3.3 (D)
unnamed: Q3.1 (G), R40.1, R41.1
unnamed: Q6.1 (G), R37.1, R42.1
unnamed: Q7.1 (B), R36.1
unnamed: Q7.3 (C), R42.2
unnamed: R17.1, SW1.3, SW1.4
unnamed: R19.2, R27.1
unnamed: R20.1, R39.2
unnamed: U1.52 (QSPI_SCLK), U2.6 (CLK)
unnamed: U1.53 (QSPI_SD0), U2.5 (DI(IO0))
unnamed: U1.55 (QSPI_SD1), U2.2 (DO(IO1))
unnamed: U1.54 (QSPI_SD2), U2.3 (IO2)
unnamed: U1.51 (QSPI_SD3), U2.7 (IO3)
unnamed: R17.2, R18.1, U1.56 (QSPI_SS), U2.1 (~CS)
unnamed: C19.1, U1.20 (XIN), Y1.3
unnamed: R22.2, U1.21 (XOUT)

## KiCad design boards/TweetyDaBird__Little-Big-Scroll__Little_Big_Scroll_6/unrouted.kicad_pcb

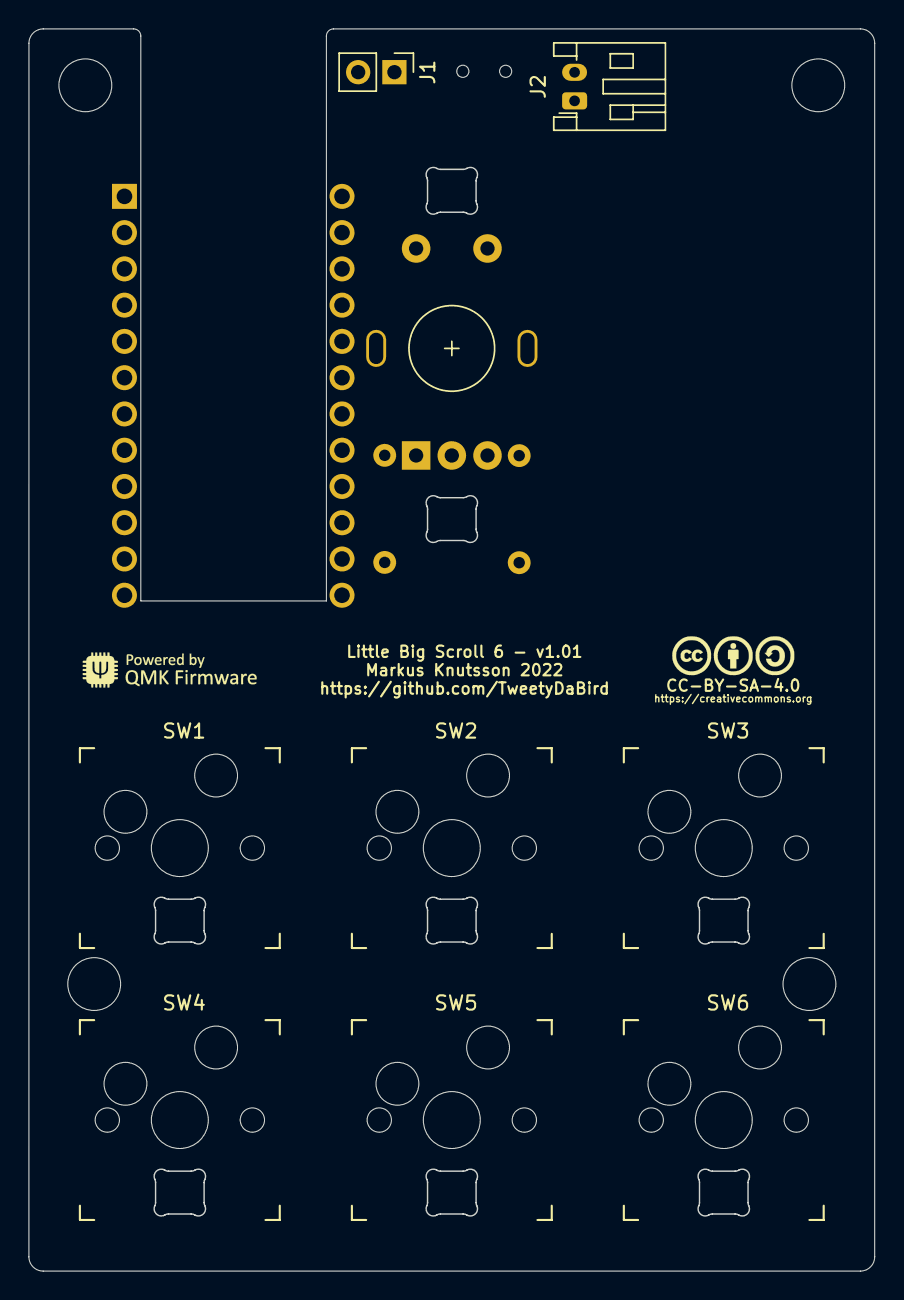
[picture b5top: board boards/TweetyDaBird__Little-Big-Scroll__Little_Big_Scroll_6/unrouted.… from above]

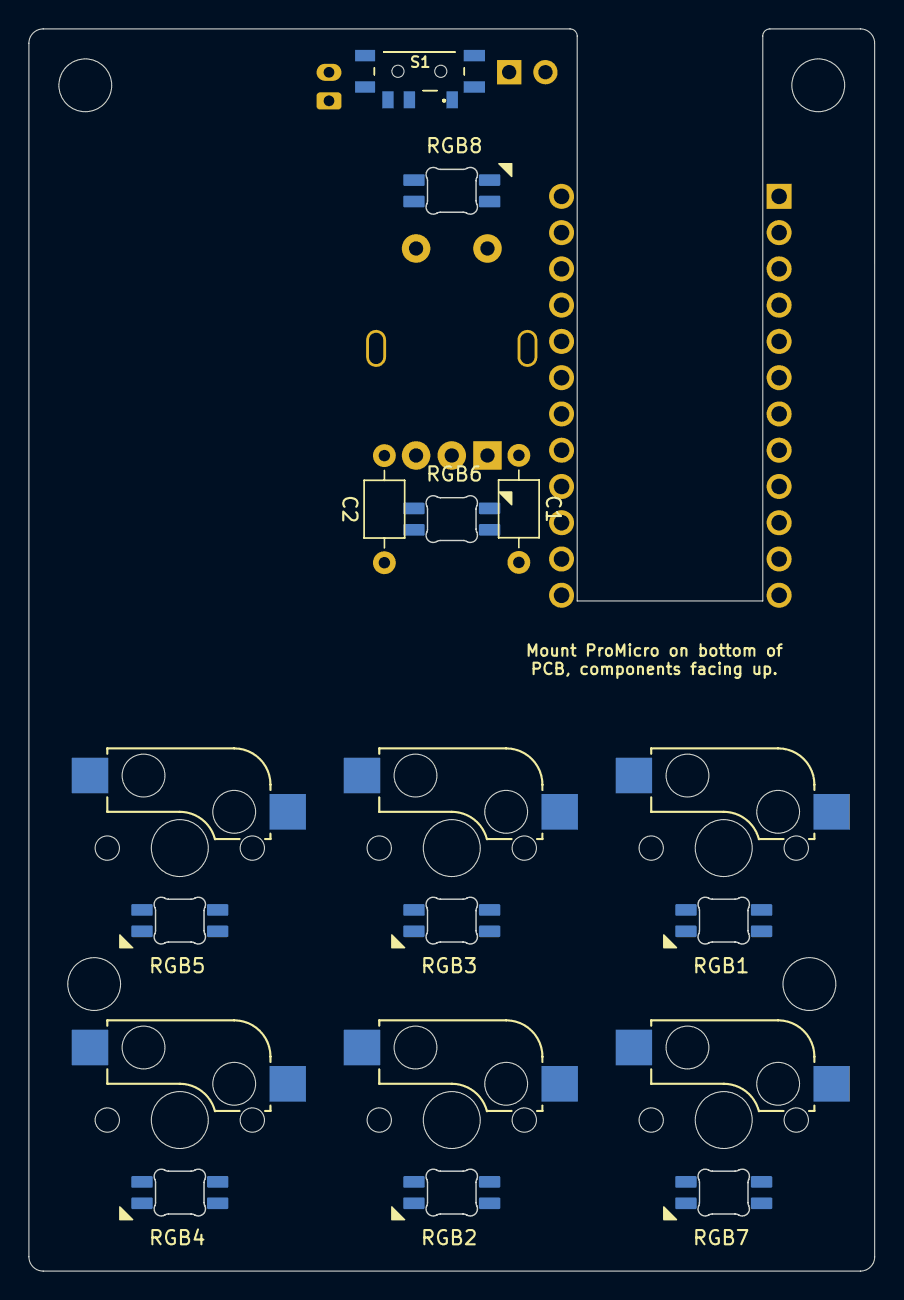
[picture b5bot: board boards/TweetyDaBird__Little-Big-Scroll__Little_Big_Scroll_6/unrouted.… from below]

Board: 2 copper layers, 59.2 x 87.0 mm, 27 parts (3 on the bottom side), 22 nets, no tracks yet.

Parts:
C1, C2: C_Small; C_Axial_L3.8mm_D2.6mm_P7.50mm_Horizontal
ENC1: Rotary_Encoder_Click; Encoder_Alps_EC11E_Small
H1, H2, H3, H4: Spacer_PCB; Spacer PCB hole
J1: Conn_01x02; PinHeader_1x02_P2.54mm_Vertical
J2: Conn_01x02; JST_PH_S2B-PH-K_1x02_P2.00mm_Horizontal
Logo1: CC-BY-SA-4.0; CC_BY_SA_40
Logo2: QMK_Logo; Powered_by_QMK
RGB1, RGB2, RGB3, RGB4, RGB5, RGB6, RGB7, RGB8: SK6812MINI-E; RGB_SK6812MINI-E
S1: MSK12C02
SW1, SW2, SW3, SW4, SW5, SW6: SW_MX_HS; SW_MX_HotSwap
U1: ProMicro; ArduinoProMicro-BackSide

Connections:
/BAT++: J2.2, S1.C1 (NO)
BAT+: S1.B1 (COM), U1.24 (RAW)
EncA: C1.1, ENC1.A, U1.17 ((A)F7)
EncB: C2.2, ENC1.B, U1.18 ((A)F6)
EncKey: ENC1.S1, U1.19 ((A)F5)
GND: C1.2, C2.1, ENC1.C, ENC1.MP1 (GND), ENC1.MP2 (GND), ENC1.S2, J1.1, J2.1, RGB1.3 (GND), RGB2.3 (GND), RGB3.3 (GND), RGB4.3 (GND), RGB5.3 (GND), RGB6.3 (GND), RGB7.3 (GND), RGB8.3 (GND), S1.MP, SW1.2, SW2.2, SW3.2, SW4.2, SW5.2, SW6.2, U1.3 (GND), U1.4 (GND), U1.23 (GND)
Key1: SW1.1, U1.8 (C6)
Key2: SW2.1, U1.10 (E6)
Key3: SW3.1, U1.12 (B5)
Key4: SW4.1, U1.7 (D4)
Key5: SW5.1, U1.9 (D7)
Key6: SW6.1, U1.11 (B4)
unnamed: RGB1.2 (DOUT), RGB3.4 (DIN)
unnamed: RGB2.2 (DOUT), RGB4.4 (DIN)
unnamed: RGB2.4 (DIN), RGB7.2 (DOUT)
unnamed: RGB3.2 (DOUT), RGB5.4 (DIN)
unnamed: RGB4.2 (DOUT), RGB6.4 (DIN)
unnamed: RGB5.2 (DOUT), RGB7.4 (DIN)
unnamed: RGB6.2 (DOUT), RGB8.4 (DIN)
unnamed: J1.2, U1.22 (RST)
RGB: RGB1.4 (DIN), U1.2 (D2(RX))
VCC: RGB1.1 (VDD), RGB2.1 (VDD), RGB3.1 (VDD), RGB4.1 (VDD), RGB5.1 (VDD), RGB6.1 (VDD), RGB7.1 (VDD), RGB8.1 (VDD), U1.21 (VCC)

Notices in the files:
boards/Spaceflight-Rocketry-Giessen-e-V__Telemetry__TelemetryGroundstationDB/unrouted.kicad_pcb:
Licensed under
CERN-OHL-S v2 or any later version:
ohwr.org/cern_ohl_s_v2.txt
boards/TweetyDaBird__Little-Big-Scroll__Little_Big_Scroll_6/unrouted.kicad_pcb:
Licensed under Creative Commons BY-SA 4.0 International
